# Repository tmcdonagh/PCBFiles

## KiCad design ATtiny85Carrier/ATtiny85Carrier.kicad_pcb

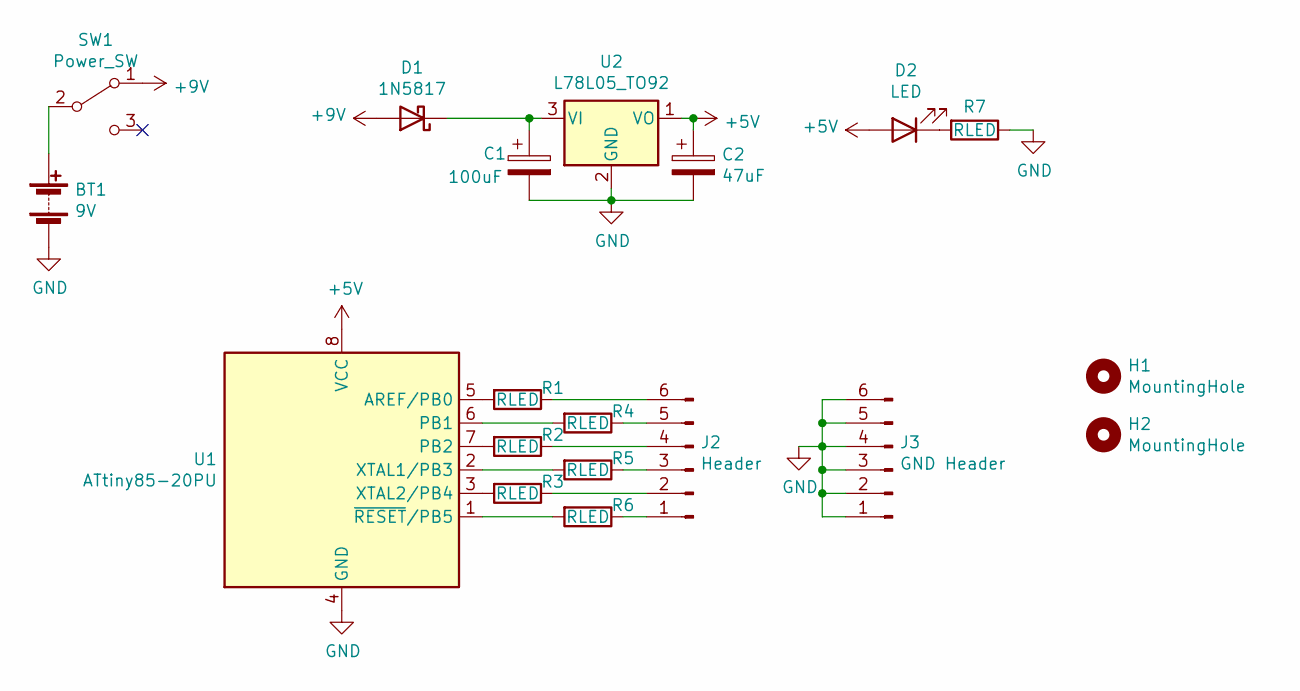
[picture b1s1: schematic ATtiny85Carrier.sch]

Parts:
BT1: 9V; PinSocket_1x02_P2.54mm_Vertical
C1: 100uF; CP_Radial_D6.3mm_P2.50mm_L11.0mm
C2: 47uF; CP_Radial_D6.3mm_P2.50mm_L11.0mm
D1: 1N5817; D_DO-41_SOD81_P10.16mm_Horizontal
D2: LED; LED_D5.0mm
H1, H2: MountingHole; MountingHole_2.5mm
J2: Header; PinSocket_1x06_P2.54mm_Vertical
J3: GND Header; PinSocket_1x06_P2.54mm_Vertical
R1, R2, R3, R4, R5, R6, R7: RLED; R_Axial_DIN0207_L6.3mm_D2.5mm_P10.16mm_Horizontal
SW1: Power_SW; MSS10255914AD
U1: ATtiny85-20PU; DIP-8_W7.62mm
U2: L78L05_TO92; TO-92_Inline

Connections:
+5V: C2.1, D2.2 (A), U1.8 (VCC), U2.1 (VO)
+9V: D1.2 (A), SW1.1 (A)
GND: BT1.2 (-), C1.2, C2.2, J3.1, J3.2, J3.3, J3.4, J3.5, J3.6, R7.1, U1.4 (GND), U2.2 (GND)
unnamed: BT1.1 (+), SW1.2 (B)
unnamed: C1.1, D1.1 (K), U2.3 (VI)
unnamed: D2.1 (K), R7.2
unnamed: J2.1, R6.1
unnamed: J2.2, R3.1
unnamed: J2.3, R5.1
unnamed: J2.4, R2.1
unnamed: J2.5, R4.1
unnamed: J2.6, R1.1
unnamed: R1.2, U1.5 (AREF/PB0)
unnamed: R2.2, U1.7 (PB2)
unnamed: R3.2, U1.3 (XTAL2/PB4)
unnamed: R4.2, U1.6 (PB1)
unnamed: R5.2, U1.2 (XTAL1/PB3)
unnamed: R6.2, U1.1 (~RESET~/PB5)

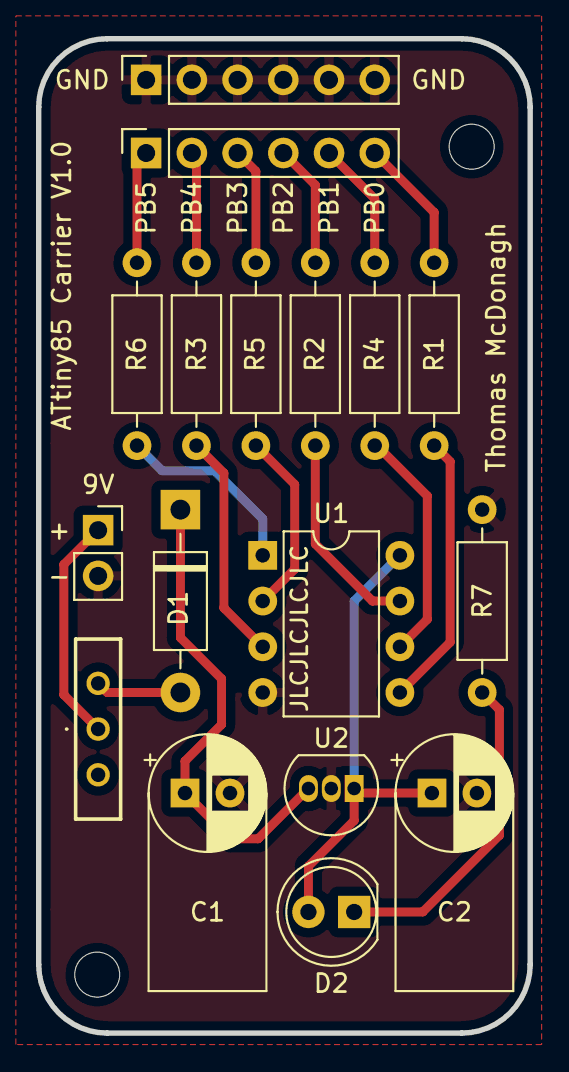
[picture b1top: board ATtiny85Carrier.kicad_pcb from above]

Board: 2 copper layers, 27.3 x 55.2 mm, 19 parts (0 on the bottom side), 18 nets.

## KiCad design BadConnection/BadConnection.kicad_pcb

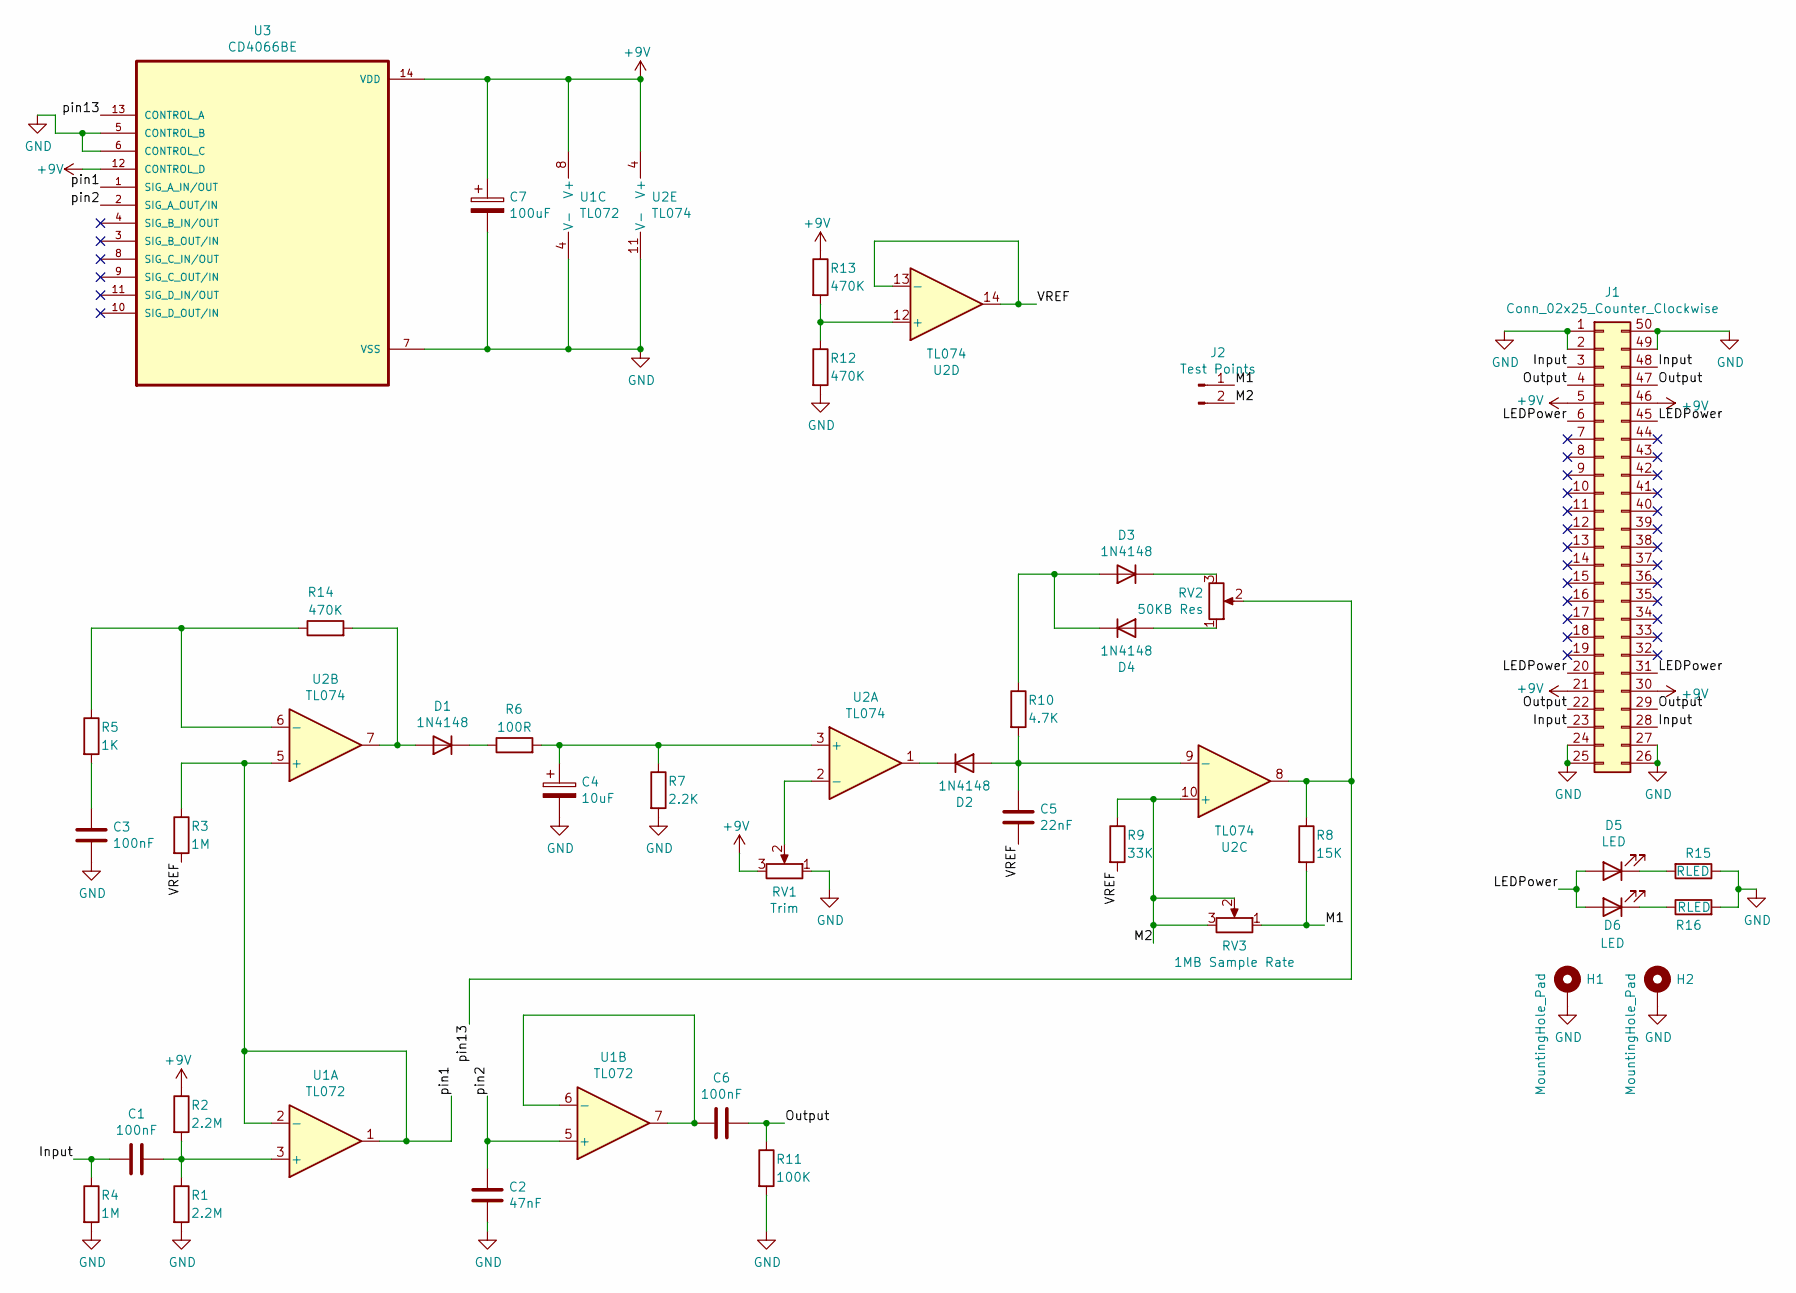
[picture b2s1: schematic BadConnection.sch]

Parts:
C1, C3, C6: 100nF; C_Flat_L7.2_H6.5
C2: 47nF; C_Flat_L7.2_H6.5
C4: 10uF; CP_Radial_D6.3mm_P2.50mm_L11.0mm
C5: 22nF; C_Flat_L7.2_H6.5
C7: 100uF; CP_Radial_D6.3mm_P2.50mm_L11.0mm
D1, D2, D3, D4: 1N4148; D_DO-35_SOD27_P7.62mm_Horizontal
D5, D6: LED; LED_D5.0mm
H1, H2: MountingHole_Pad; MountingHole_2.5mm_Pad
J1: Conn_02x25_Counter_Clockwise; N64-Connector-Wide
J2: Test Points; PinSocket_1x02_P2.54mm_Vertical
R1, R2: 2.2M; R_Axial_DIN0207_L6.3mm_D2.5mm_P10.16mm_Horizontal
R3, R4: 1M; R_Axial_DIN0207_L6.3mm_D2.5mm_P10.16mm_Horizontal
R5: 1K; R_Axial_DIN0207_L6.3mm_D2.5mm_P10.16mm_Horizontal
R6: 100R; R_Axial_DIN0207_L6.3mm_D2.5mm_P10.16mm_Horizontal
R7: 2.2K; R_Axial_DIN0207_L6.3mm_D2.5mm_P10.16mm_Horizontal
R8: 15K; R_Axial_DIN0207_L6.3mm_D2.5mm_P10.16mm_Horizontal
R9: 33K; R_Axial_DIN0207_L6.3mm_D2.5mm_P10.16mm_Horizontal
R10: 4.7K; R_Axial_DIN0207_L6.3mm_D2.5mm_P10.16mm_Horizontal
R11: 100K; R_Axial_DIN0207_L6.3mm_D2.5mm_P10.16mm_Horizontal
R12, R13, R14: 470K; R_Axial_DIN0207_L6.3mm_D2.5mm_P10.16mm_Horizontal
R15, R16: RLED; R_Axial_DIN0207_L6.3mm_D2.5mm_P10.16mm_Horizontal
RV1: Trim; Potentiometer_Bourns_3386F_Vertical
RV2: 50KB Res; Potentiometer_Bourns_PTV09A-1_Single_Vertical
RV3: 1MB Sample Rate; Potentiometer_Bourns_PTV09A-1_Single_Vertical
U1: TL072; DIP-8_W7.62mm
U2: TL074; DIP-14_W7.62mm
U3: CD4066BE; DIP-14_W7.62mm

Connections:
+9V: C7.1, J1.5, J1.21, J1.30, J1.46, R2.1, R13.1, RV1.3, U1.8 (V+), U2.4 (V+), U3.12 (CONTROL_D), U3.14 (VDD)
/Input: C1.2, J1.3, J1.23, J1.28, J1.48, R4.1
/LEDPower: D5.2 (A), D6.2 (A), J1.6, J1.20, J1.31, J1.45
/M1: J2.1, R8.2, RV3.1
/M2: J2.2, R9.1, RV3.2, RV3.3, U2.10 (+)
/Output: C6.1, J1.4, J1.22, J1.29, J1.47, R11.1
/VREF: C5.1, R3.2, R9.2, U2.13 (-), U2.14
/pin1: R3.1, U1.1, U1.2 (-), U2.5 (+), U3.1 (SIG_A_IN/OUT)
/pin2: C2.2, U1.5 (+), U3.2 (SIG_A_OUT/IN)
/pin13: R8.1, RV2.2, U2.8, U3.13 (CONTROL_A)
GND: C2.1, C3.1, C4.2, C7.2, H1.1, H2.1, J1.1, J1.2, J1.24, J1.25, J1.26, J1.27, J1.49, J1.50, R1.2, R4.2, R7.2, R11.2, R12.2, R15.1, R16.2, RV1.1, U1.4 (V-), U2.11 (V-), U3.5 (CONTROL_B), U3.6 (CONTROL_C), U3.7 (VSS)
unnamed: C1.1, R1.1, R2.2, U1.3 (+)
unnamed: C3.2, R5.2
unnamed: C4.1, R6.2, R7.1, U2.3 (+)
unnamed: C5.2, D2.2 (A), R10.2, U2.9 (-)
unnamed: C6.2, U1.6 (-), U1.7
unnamed: D1.1 (K), R6.1
unnamed: D1.2 (A), R14.2, U2.7
unnamed: D2.1 (K), U2.1
unnamed: D3.1 (K), RV2.3
unnamed: D3.2 (A), D4.1 (K), R10.1
unnamed: D4.2 (A), RV2.1
unnamed: D5.1 (K), R15.2
unnamed: D6.1 (K), R16.1
unnamed: R12.1, R13.2, U2.12 (+)
unnamed: R5.1, R14.1, U2.6 (-)
unnamed: RV1.2, U2.2 (-)

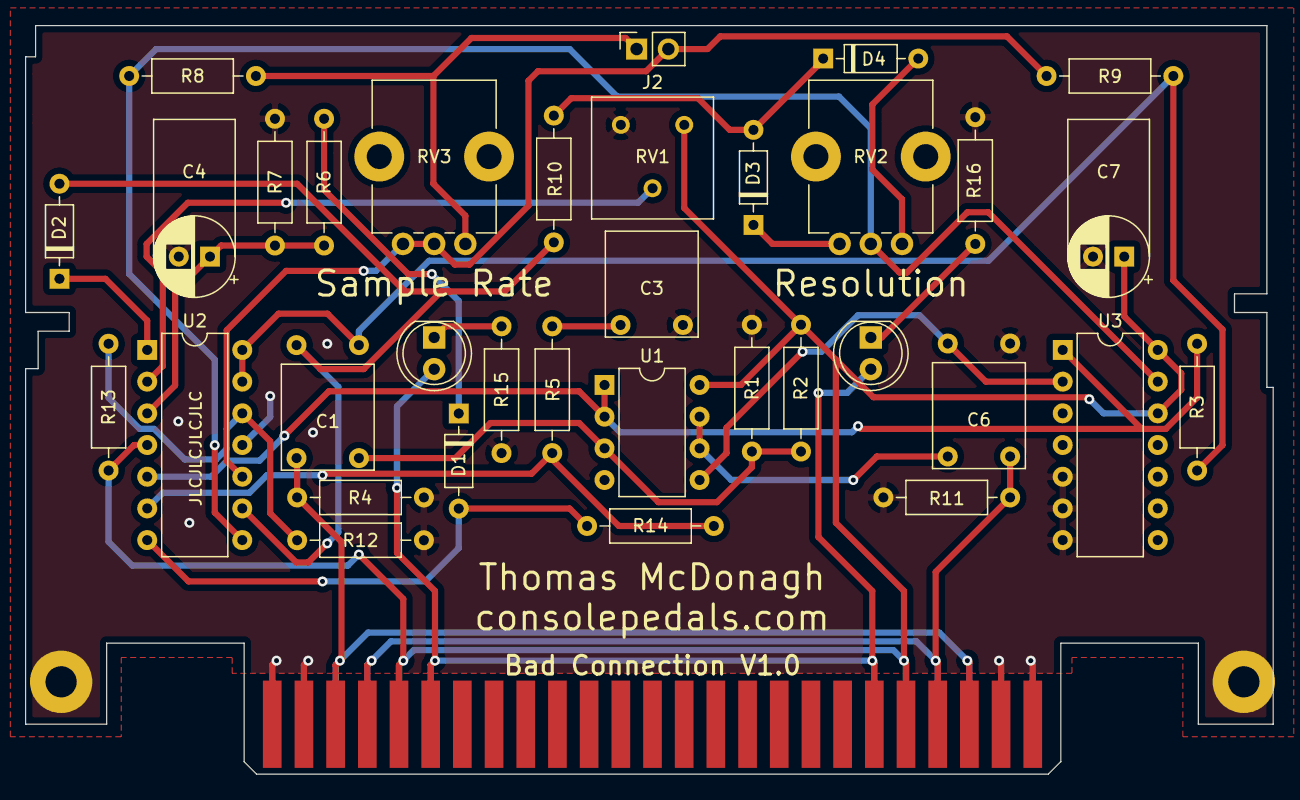
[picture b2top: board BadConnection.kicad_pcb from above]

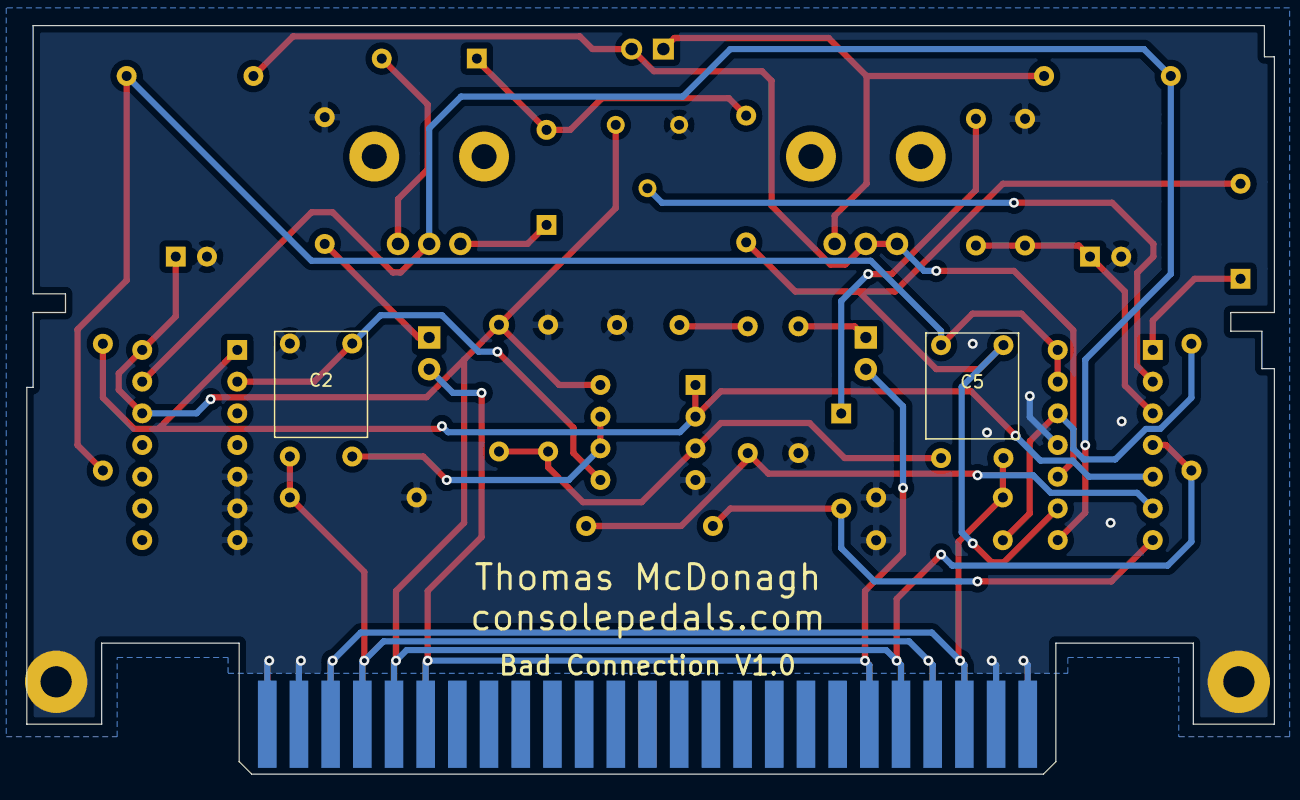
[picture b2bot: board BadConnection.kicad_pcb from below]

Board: 2 copper layers, 100.0 x 60.0 mm, 39 parts (2 on the bottom side), 27 nets.

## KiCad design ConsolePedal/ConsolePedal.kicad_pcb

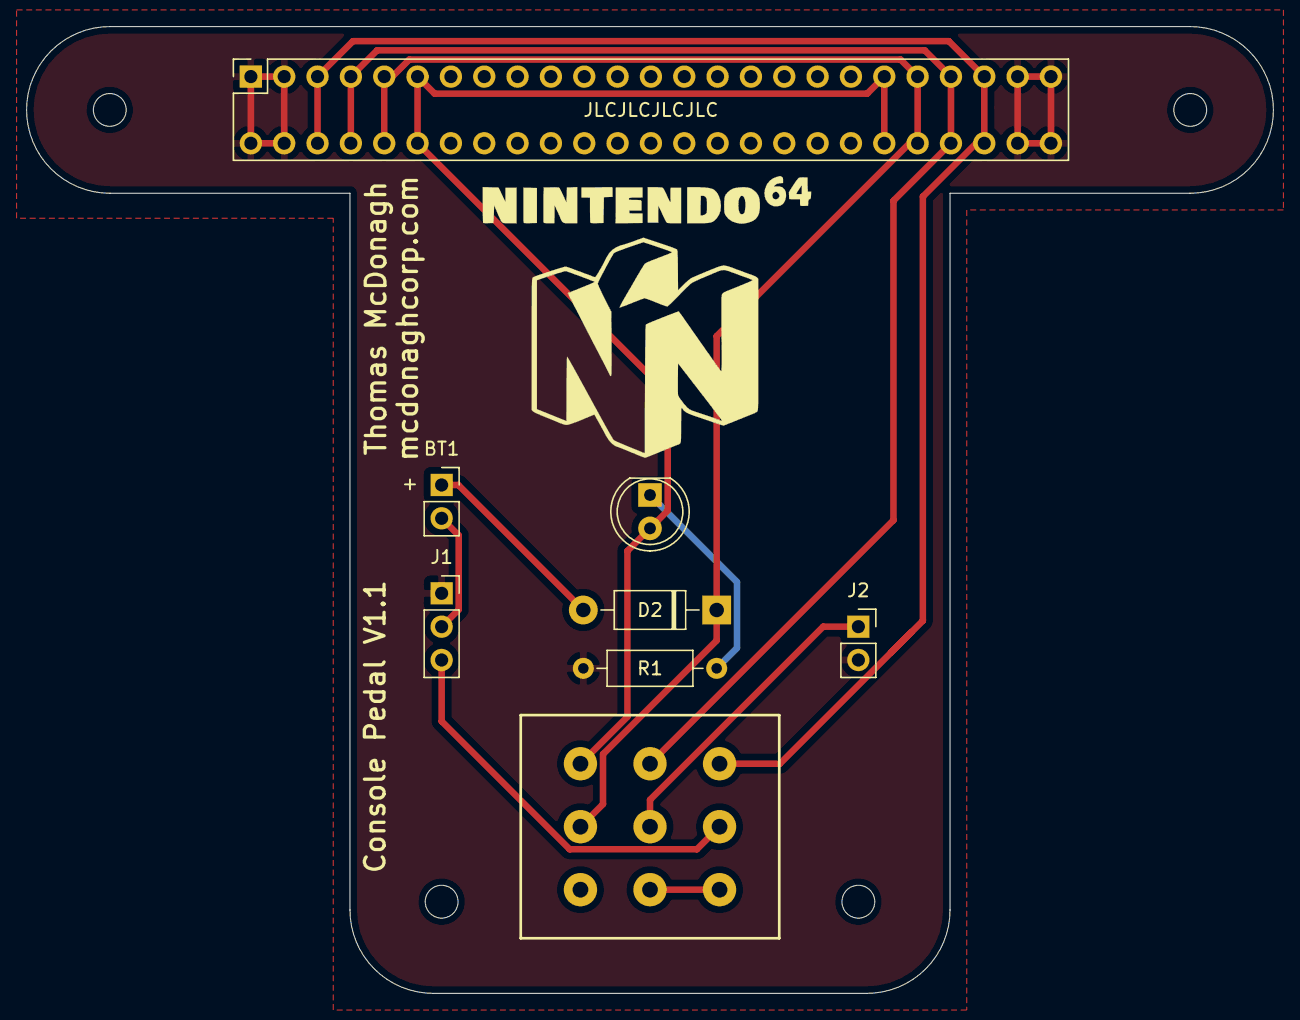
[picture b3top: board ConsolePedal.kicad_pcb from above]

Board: 2 copper layers, 95.0 x 73.7 mm, 8 parts (0 on the bottom side), 11 nets.

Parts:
BT1: Battery; PinSocket_1x02_P2.54mm_Vertical
D1: LED; LED_D5.0mm
D2: D; D_DO-41_SOD81_P10.16mm_Horizontal
J1: AudioJack3; PinSocket_1x03_P2.54mm_Vertical
J2: AudioJack2; PinSocket_1x02_P2.54mm_Vertical
J3: Conn_02x25_Odd_Even; n64Socket
R1: R; R_Axial_DIN0207_L6.3mm_D2.5mm_P10.16mm_Horizontal
S1: SWITCH-3PDT-PTH-STOMP; STOMP_SWITCH_3PDT

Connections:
+9V: D2.1, J3.9, J3.10, J3.41, J3.42, S1.P$8
/Input: J3.5, J3.6, J3.45, J3.46, S1.P$3
/LEDPower: D1.2, J3.11, J3.12, J3.39, J3.40, S1.P$9
/Output: J3.7, J3.8, J3.43, J3.44, S1.P$6
GND: J1.1, J2.2, J3.1, J3.2, J3.3, J3.4, J3.47, J3.48, J3.49, J3.50, R1.2
unnamed: BT1.1, D2.2
unnamed: BT1.2, J1.2
unnamed: D1.1, R1.1
unnamed: J1.3, S1.P$2
unnamed: J2.1, S1.P$5
unnamed: S1.P$1, S1.P$4

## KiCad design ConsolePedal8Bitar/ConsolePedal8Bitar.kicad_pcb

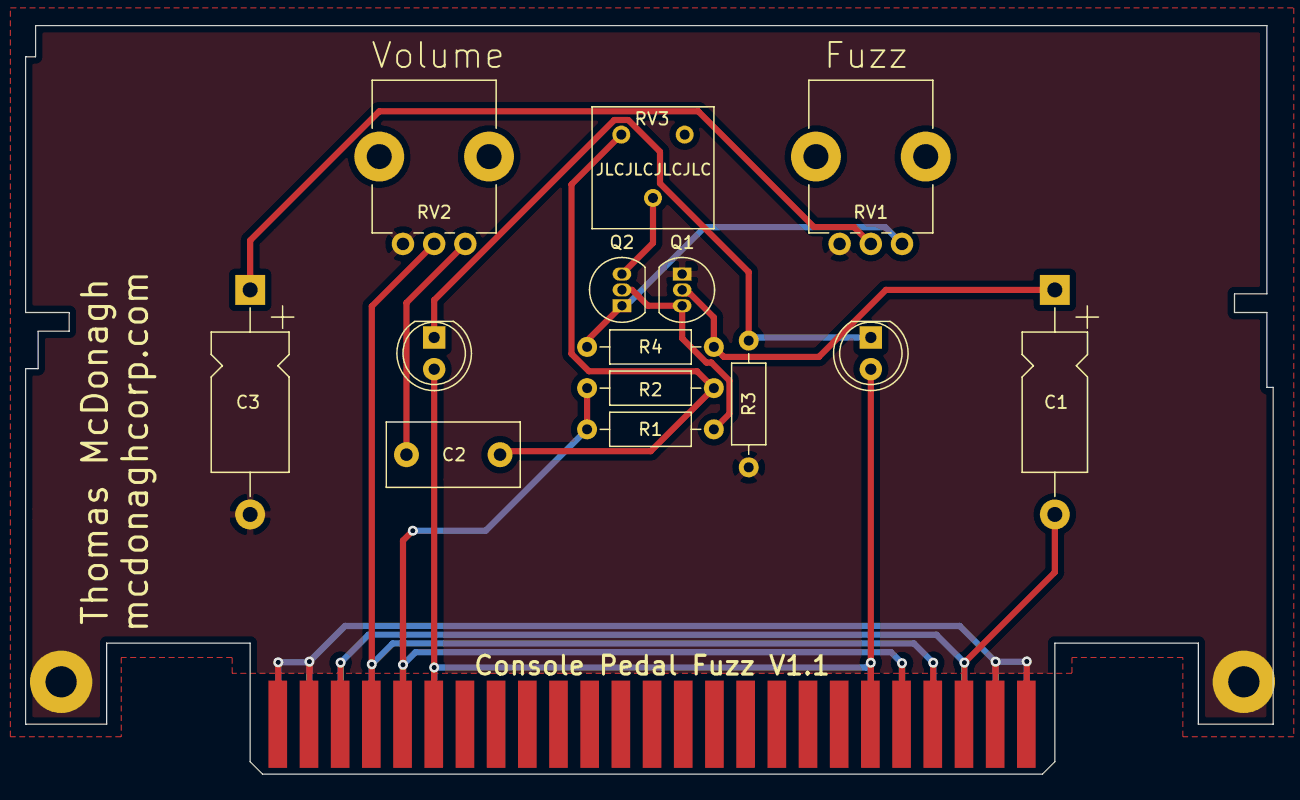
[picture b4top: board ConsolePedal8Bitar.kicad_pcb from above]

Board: 2 copper layers, 100.0 x 60.0 mm, 17 parts (0 on the bottom side), 13 nets.

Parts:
C1: 2.2uF; CP_Axial_L11.0mm_D5.0mm_P18.00mm_Horizontal
C2: 0.01uF; C_Disc_D10.5mm_W5.0mm_P7.50mm
C3: 22uF; CP_Axial_L11.0mm_D6.0mm_P18.00mm_Horizontal
D1, D2: LED; LED_D5.0mm
H1, H2: MountingHole_Pad; MountingHole_2.5mm_Pad
J1: Conn_02x25_Counter_Clockwise; N64-Connector
Q1, Q2: 2N3904; TO-92_Inline
R1: 33K; R_Axial_DIN0207_L6.3mm_D2.5mm_P10.16mm_Horizontal
R2: 330; R_Axial_DIN0207_L6.3mm_D2.5mm_P10.16mm_Horizontal
R3, R4: 100K; R_Axial_DIN0207_L6.3mm_D2.5mm_P10.16mm_Horizontal
RV1: 1K; Potentiometer_Bourns_PTV09A-1_Single_Vertical
RV2: 500K; Potentiometer_Bourns_PTV09A-1_Single_Vertical
RV3: 10K; Potentiometer_Bourns_3386F_Vertical

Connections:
+9V: J1.5, J1.21, J1.30, J1.46, R1.2, R2.2
/Input: C1.2, J1.3, J1.23, J1.28, J1.48
/LEDPower: D1.2, D2.2, J1.6, J1.20, J1.31, J1.45
/Output: J1.4, J1.22, J1.29, J1.47, RV2.2
GND: C3.2, H1.1, H2.1, J1.1, J1.2, J1.24, J1.25, J1.26, J1.27, J1.49, J1.50, Q1.1, R3.1, RV1.3, RV2.3
unnamed: C1.1, Q1.2, R4.1
unnamed: C2.1, RV2.1
unnamed: C2.2, R2.1, RV3.1
unnamed: C3.1, RV1.2
unnamed: D1.1, D2.1, R3.2
unnamed: Q1.3, Q2.2, R1.1
unnamed: Q2.1, R4.2, RV1.1
unnamed: Q2.3, RV3.2

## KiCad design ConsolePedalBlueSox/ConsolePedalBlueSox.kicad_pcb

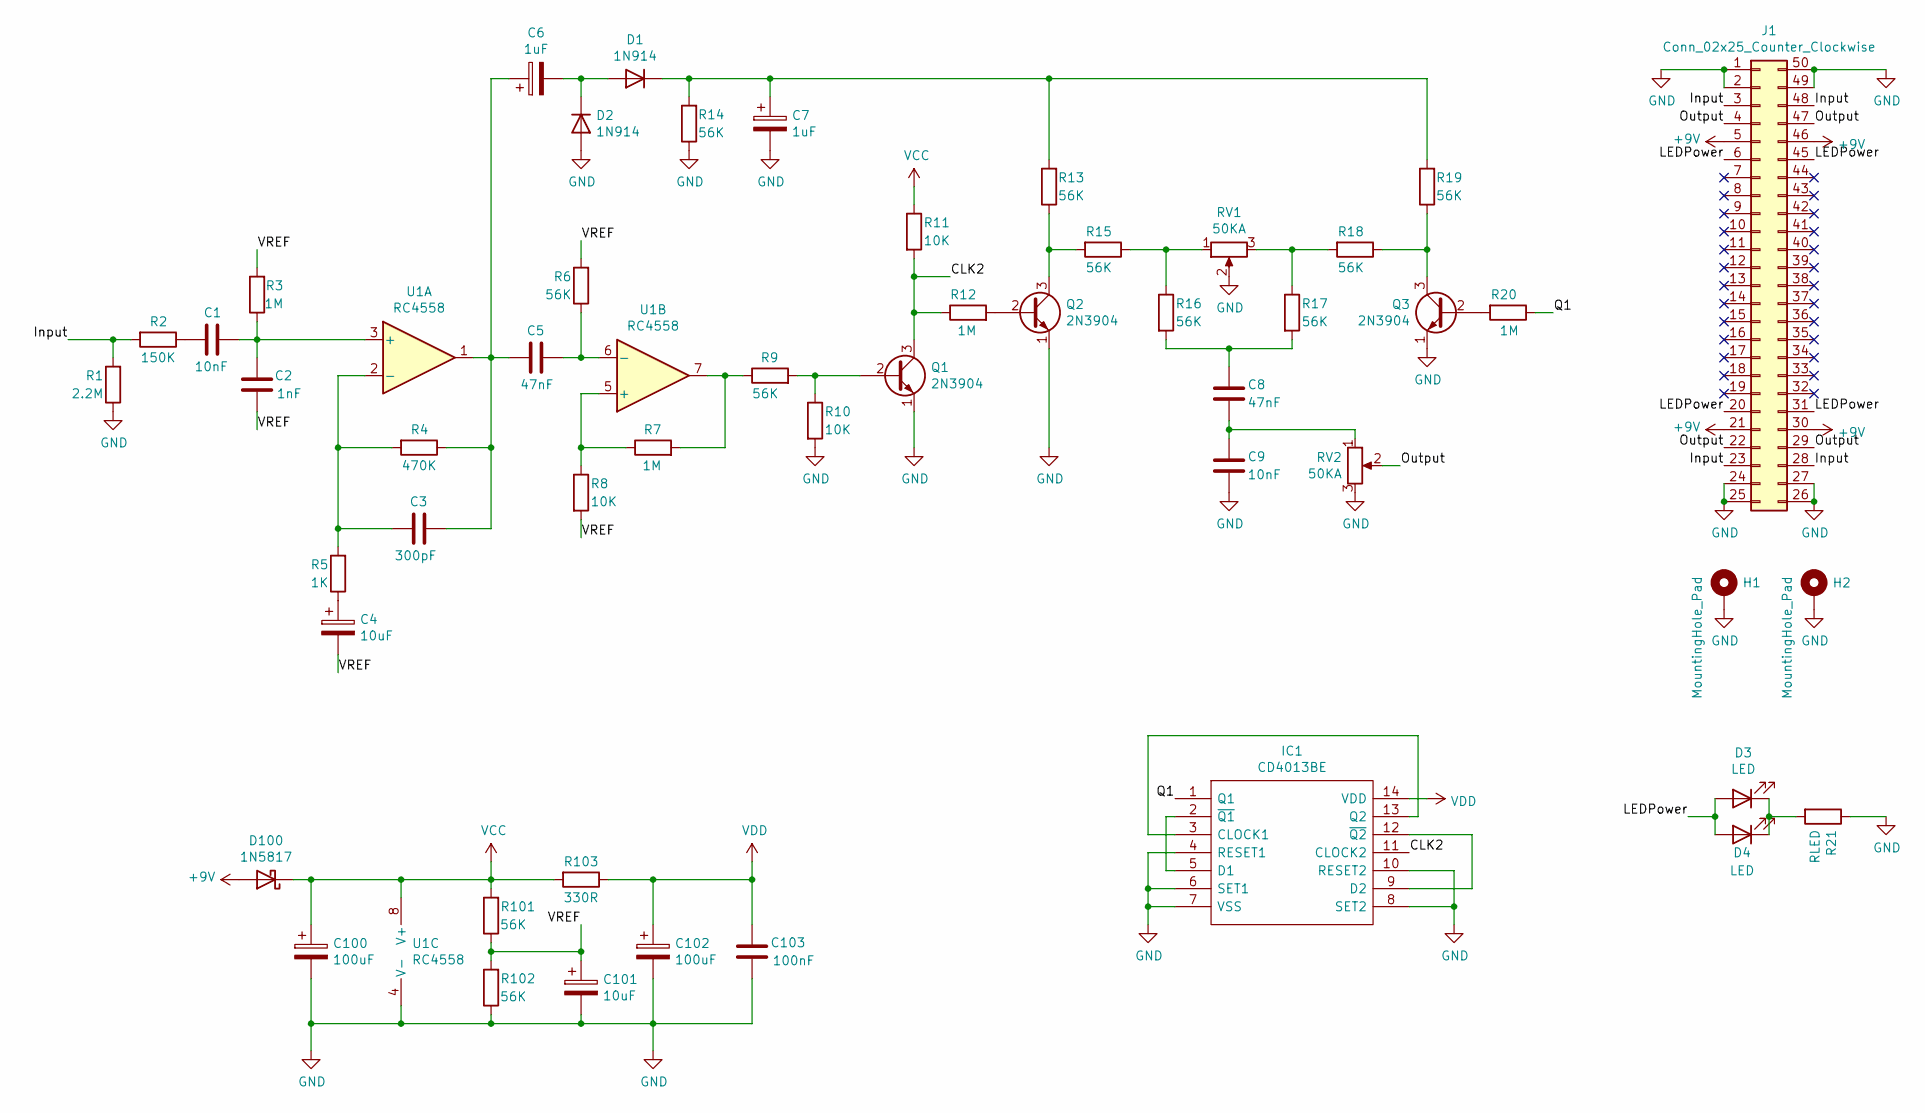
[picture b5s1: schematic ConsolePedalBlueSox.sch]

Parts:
C1, C9: 10nF; C_Flat_L7.2_H6.5
C2: 1nF; C_Flat_L7.2_H6.5
C3: 300pF; C_Flat_L7.2_H6.5
C4, C101: 10uF
C5, C8: 47nF; C_Flat_L7.2_H6.5
C6, C7: 1uF
C100, C102: 100uF
C103: 100nF; C_Flat_L7.2_H6.5
D1, D2: 1N914; D_DO-35_SOD27_P7.62mm_Horizontal
D3, D4: LED; LED_D5.0mm
D100: 1N5817; D_DO-41_SOD81_P10.16mm_Horizontal
H1, H2: MountingHole_Pad; MountingHole_2.5mm_Pad
IC1: CD4013BE; DIP-14_W7.62mm; Mouser Part Number 595-CD4013BE
J1: Conn_02x25_Counter_Clockwise; N64-Connector-Wide
Q1, Q2, Q3: 2N3904; TO-92_Inline
R1: 2.2M; R_Axial_DIN0207_L6.3mm_D2.5mm_P10.16mm_Horizontal
R2: 150K; R_Axial_DIN0207_L6.3mm_D2.5mm_P10.16mm_Horizontal
R3, R7, R12, R20: 1M; R_Axial_DIN0207_L6.3mm_D2.5mm_P10.16mm_Horizontal
R4: 470K; R_Axial_DIN0207_L6.3mm_D2.5mm_P10.16mm_Horizontal
R5: 1K; R_Axial_DIN0207_L6.3mm_D2.5mm_P10.16mm_Horizontal
R6, R9, R13, R14, R15, R16, R17, R18, R19, R101, R102: 56K; R_Axial_DIN0207_L6.3mm_D2.5mm_P10.16mm_Horizontal
R8, R10, R11: 10K; R_Axial_DIN0207_L6.3mm_D2.5mm_P10.16mm_Horizontal
R21: RLED; R_Axial_DIN0207_L6.3mm_D2.5mm_P10.16mm_Horizontal
R103: 330R; R_Axial_DIN0207_L6.3mm_D2.5mm_P10.16mm_Horizontal
RV1, RV2: 50KA; Potentiometer_Bourns_PTV09A-1_Single_Vertical
U1: RC4558; DIP-8_W7.62mm

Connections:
+9V: D100.2 (A), J1.5, J1.21, J1.30, J1.46
/CLK2: IC1.11 (CLOCK2), Q1.3 (C), R11.2, R12.1
/Input: J1.3, J1.23, J1.28, J1.48, R1.2, R2.2
/LEDPower: D3.2 (A), D4.2 (A), J1.6, J1.20, J1.31, J1.45
/Output: J1.4, J1.22, J1.29, J1.47, RV2.2
/Q1: IC1.1 (Q1), R20.1
/VREF: C2.1, C4.2, C101.1, R3.2, R6.2, R8.2, R101.1, R102.2
GND: C7.2, C9.2, C100.2, C101.2, C102.2, C103.1, D2.2 (A), H1.1, H2.1, IC1.4 (RESET1), IC1.6 (SET1), IC1.7 (VSS), IC1.8 (SET2), IC1.10 (RESET2), J1.1, J1.2, J1.24, J1.25, J1.26, J1.27, J1.49, J1.50, Q1.1 (E), Q2.1 (E), Q3.1 (E), R1.1, R10.2, R14.1, R21.1, R102.1, RV1.2, RV2.3, U1.4 (V-)
unnamed: C1.1, C2.2, R3.1, U1.3 (+)
unnamed: C1.2, R2.1
unnamed: C3.1, R4.2, R5.2, U1.2 (-)
unnamed: C3.2, C5.1, C6.1, R4.1, U1.1
unnamed: C4.1, R5.1
unnamed: C5.2, R6.1, U1.6 (-)
unnamed: C6.2, D1.2 (A), D2.1 (K)
unnamed: C7.1, D1.1 (K), R13.2, R14.2, R19.2
unnamed: C8.1, R16.2, R17.2
unnamed: C8.2, C9.1, RV2.1
unnamed: D3.1 (K), D4.1 (K), R21.2
unnamed: IC1.2 (~Q1), IC1.5 (D1)
unnamed: IC1.9 (D2), IC1.12 (~Q2)
unnamed: IC1.3 (CLOCK1), IC1.13 (Q2)
unnamed: Q1.2 (B), R9.2, R10.1
unnamed: Q2.2 (B), R12.2
unnamed: Q2.3 (C), R13.1, R15.2
unnamed: Q3.2 (B), R20.2
unnamed: Q3.3 (C), R18.1, R19.1
unnamed: R7.1, R8.1, U1.5 (+)
unnamed: R7.2, R9.1, U1.7
unnamed: R15.1, R16.1, RV1.1
unnamed: R17.1, R18.2, RV1.3
VCC: C100.1, D100.1 (K), R11.1, R101.2, R103.2, U1.8 (V+)
VDD: C102.1, C103.2, IC1.14 (VDD), R103.1

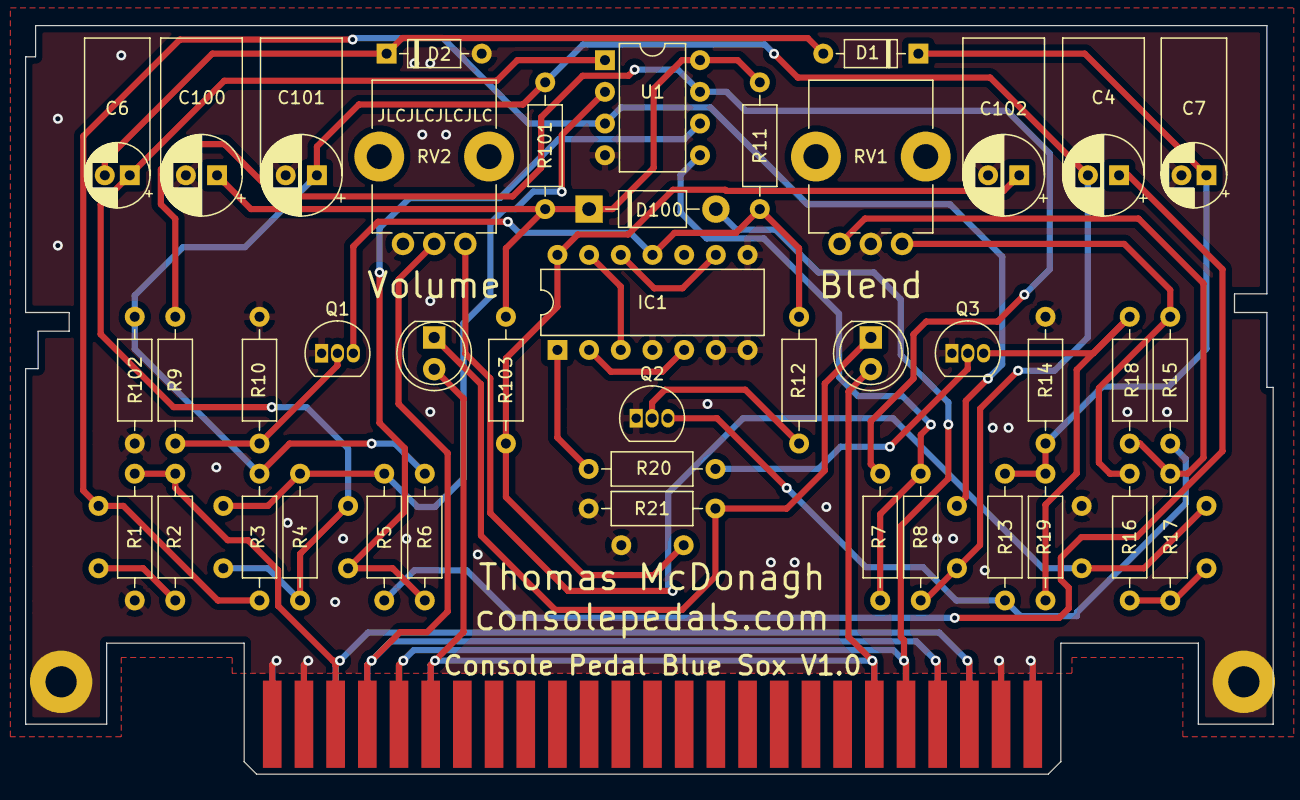
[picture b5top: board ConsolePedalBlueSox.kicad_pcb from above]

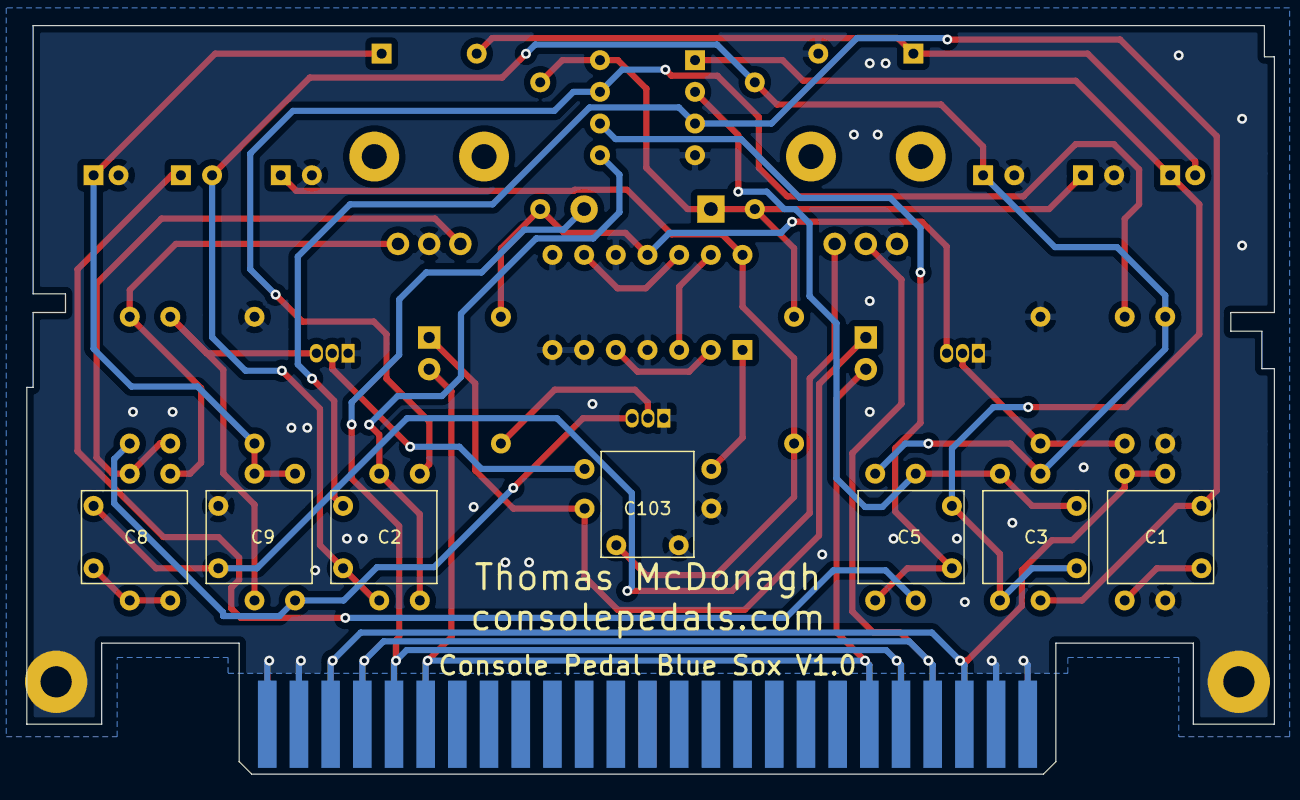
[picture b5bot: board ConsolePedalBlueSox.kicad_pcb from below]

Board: 2 copper layers, 100.0 x 60.0 mm, 52 parts (7 on the bottom side), 33 nets.

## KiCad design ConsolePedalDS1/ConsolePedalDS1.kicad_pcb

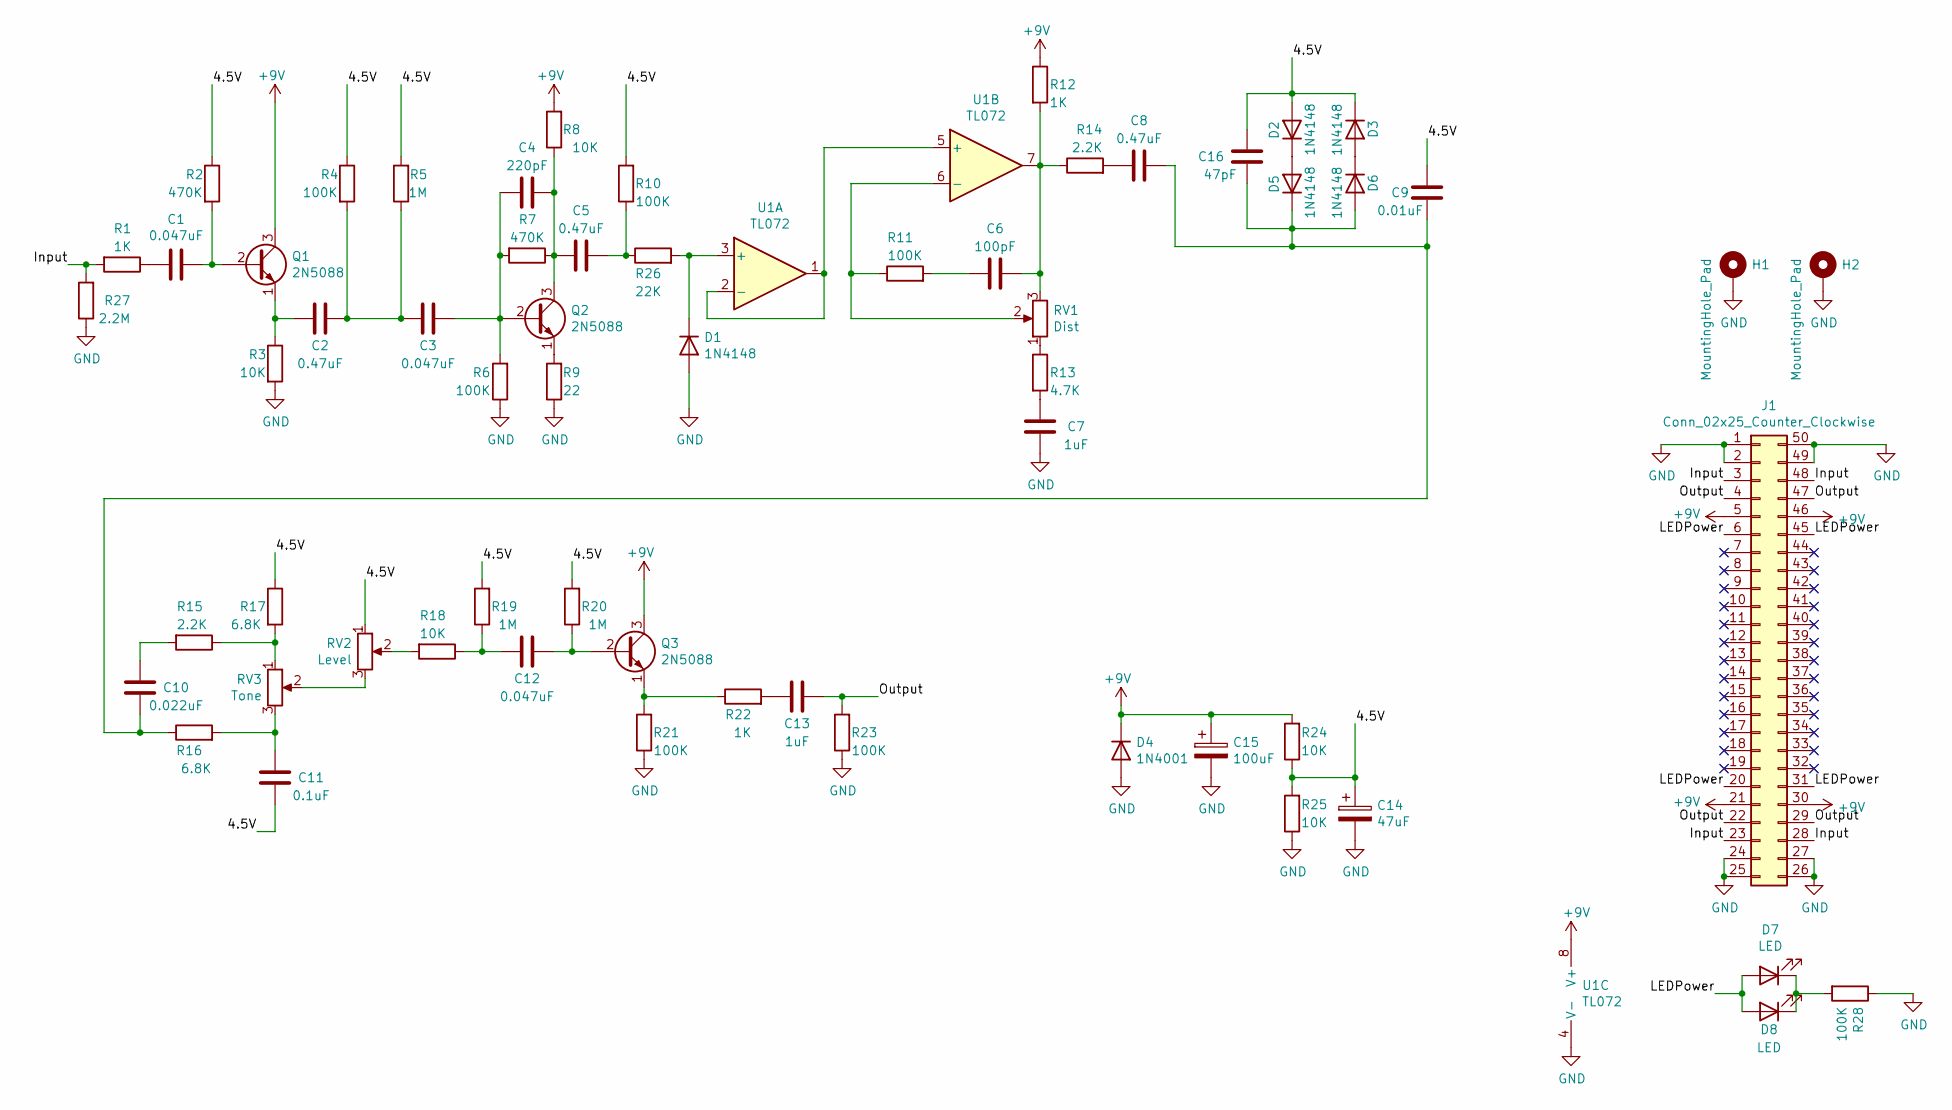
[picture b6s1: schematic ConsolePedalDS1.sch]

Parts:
C1, C3, C12: 0.047uF; C_Flat_L7.2_H6.5
C2, C5, C8: 0.47uF; C_Flat_L7.2_H6.5
C4: 220pF; C_Axial_L5.1mm_D3.1mm_P7.50mm_Horizontal
C6: 100pF; C_Axial_L3.8mm_D2.6mm_P7.50mm_Horizontal
C7, C13: 1uF; C_Flat_L7.2_H10
C9: 0.01uF; C_Flat_L7.2_H6.5
C10: 0.022uF; C_Flat_L7.2_H6.5
C11: 0.1uF; C_Flat_L7.2_H6.5
C14: 47uF; CP_Radial_D6.3mm_P2.50mm_L7.0mm
C15: 100uF; CP_Radial_D6.3mm_P2.00mm_L11.0mm
C16: 47pF; C_Axial_L3.8mm_D2.6mm_P7.50mm_Horizontal
D1, D2, D3, D5, D6: 1N4148; D_DO-35_SOD27_P7.62mm_Horizontal
D4: 1N4001; D_DO-41_SOD81_P10.16mm_Horizontal
D7, D8: LED; LED_D5.0mm
H1, H2: MountingHole_Pad; MountingHole_2.5mm_Pad
J1: Conn_02x25_Counter_Clockwise; N64-Connector
Q1, Q2, Q3: 2N5088; TO-92_Inline
R1, R12, R22: 1K; R_Axial_DIN0207_L6.3mm_D2.5mm_P10.16mm_Horizontal
R2, R7: 470K; R_Axial_DIN0207_L6.3mm_D2.5mm_P10.16mm_Horizontal
R3, R8, R18, R24, R25: 10K; R_Axial_DIN0207_L6.3mm_D2.5mm_P10.16mm_Horizontal
R4, R6, R10, R11, R21, R23, R28: 100K; R_Axial_DIN0207_L6.3mm_D2.5mm_P10.16mm_Horizontal
R5, R19, R20: 1M; R_Axial_DIN0207_L6.3mm_D2.5mm_P10.16mm_Horizontal
R9: 22; R_Axial_DIN0207_L6.3mm_D2.5mm_P10.16mm_Horizontal
R13: 4.7K; R_Axial_DIN0207_L6.3mm_D2.5mm_P10.16mm_Horizontal
R14, R15: 2.2K; R_Axial_DIN0207_L6.3mm_D2.5mm_P10.16mm_Horizontal
R16, R17: 6.8K; R_Axial_DIN0207_L6.3mm_D2.5mm_P10.16mm_Horizontal
R26: 22K; R_Axial_DIN0207_L6.3mm_D2.5mm_P10.16mm_Horizontal
R27: 2.2M; R_Axial_DIN0207_L6.3mm_D2.5mm_P10.16mm_Horizontal
RV1: Dist; Potentiometer_Bourns_PTV09A-1_Single_Vertical
RV2: Level; Potentiometer_Bourns_PTV09A-1_Single_Vertical
RV3: Tone; Potentiometer_Bourns_PTV09A-1_Single_Vertical
U1: TL072; DIP-8_W7.62mm_Socket

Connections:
+9V: C15.1, D4.1 (K), J1.5, J1.21, J1.30, J1.46, Q1.3 (C), Q3.3 (C), R8.2, R12.1, R24.2, U1.8 (V+)
/4.5V: C9.1, C11.1, C14.1, C16.1, D2.2 (A), D3.1 (K), R2.1, R4.1, R5.2, R10.2, R17.1, R19.2, R20.2, R24.1, R25.2, RV2.1
/Input: J1.3, J1.23, J1.28, J1.48, R1.2, R27.2
/LEDPower: D7.2 (A), D8.2 (A), J1.6, J1.20, J1.31, J1.45
/Output: C13.2, J1.4, J1.22, J1.29, J1.47, R23.2
GND: C7.1, C14.2, C15.2, D1.2 (A), D4.2 (A), H1.1, H2.1, J1.1, J1.2, J1.24, J1.25, J1.26, J1.27, J1.49, J1.50, R3.2, R6.1, R9.1, R21.1, R23.1, R25.1, R27.1, R28.1, U1.4 (V-)
unnamed: C1.1, Q1.2 (B), R2.2
unnamed: C1.2, R1.1
unnamed: C2.1, Q1.1 (E), R3.1
unnamed: C2.2, C3.1, R4.2, R5.1
unnamed: C3.2, C4.2, Q2.2 (B), R6.2, R7.2
unnamed: C4.1, C5.2, Q2.3 (C), R7.1, R8.1
unnamed: C5.1, R10.1, R26.1
unnamed: C6.1, R12.2, R14.1, RV1.3, U1.7
unnamed: C6.2, R11.2
unnamed: C7.2, R13.2
unnamed: C8.2, R14.2
unnamed: C8.1, C9.2, C10.1, C16.2, D5.1 (K), D6.2 (A), R16.1
unnamed: C10.2, R15.2
unnamed: C11.2, R16.2, RV3.3
unnamed: C12.1, R18.1, R19.1
unnamed: C12.2, Q3.2 (B), R20.1
unnamed: C13.1, R22.2
unnamed: D1.1 (K), R26.2, U1.3 (+)
unnamed: D2.1 (K), D5.2 (A)
unnamed: D3.2 (A), D6.1 (K)
unnamed: D7.1 (K), D8.1 (K), R28.2
unnamed: Q2.1 (E), R9.2
unnamed: Q3.1 (E), R21.2, R22.1
unnamed: R11.1, RV1.2, U1.6 (-)
unnamed: R13.1, RV1.1
unnamed: R15.1, R17.2, RV3.1
unnamed: R18.2, RV2.2
unnamed: RV2.3, RV3.2
unnamed: U1.1, U1.2 (-), U1.5 (+)
